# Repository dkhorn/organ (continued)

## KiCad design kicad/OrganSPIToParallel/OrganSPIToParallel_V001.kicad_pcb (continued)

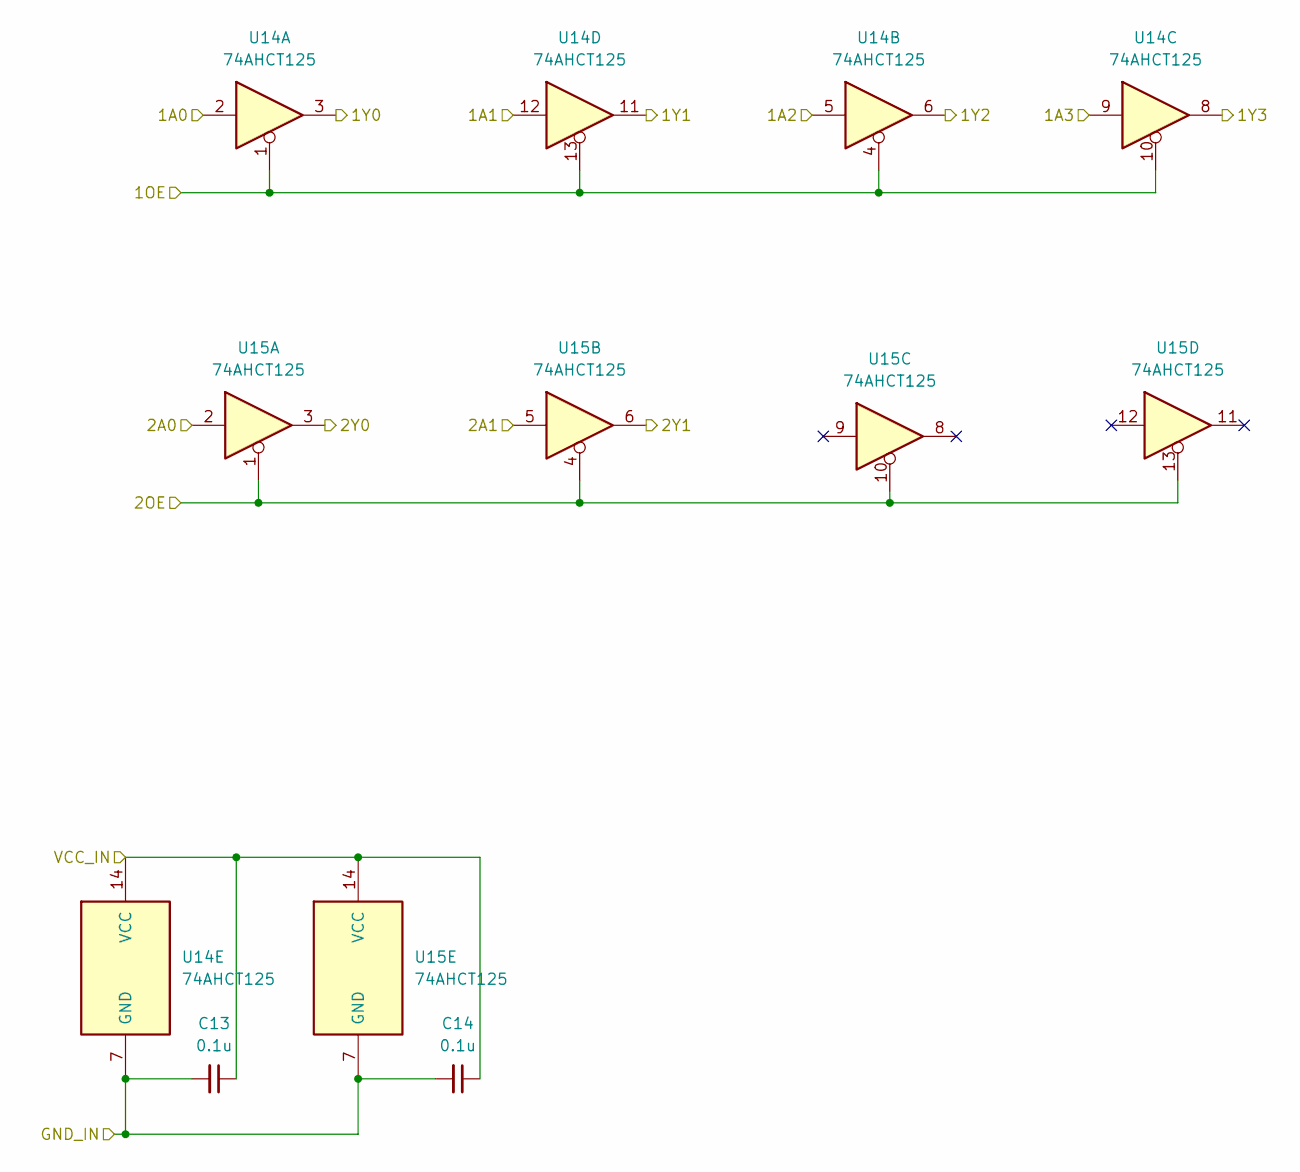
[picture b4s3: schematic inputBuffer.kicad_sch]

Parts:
C13, C14: 0.1u; C_0805_2012Metric
U14, U15: 74AHCT125; DIP-14_W7.62mm

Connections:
+5V: C13.1, C14.1, U14.14 (VCC), U15.14 (VCC); also elsewhere on the board
/CARRY_IN: U15.5; also elsewhere on the board
/LATCH_IN: U14.9; also elsewhere on the board
/MOSI_IN: U15.2; also elsewhere on the board
/OE_N_IN: U14.5; also elsewhere on the board
/SCK_IN: U14.12; also elsewhere on the board
/SRCLR_IN: U14.2; also elsewhere on the board
GND: C13.2, C14.2, U14.1, U14.4, U14.7 (GND), U14.10, U14.13, U15.1, U15.4, U15.7 (GND), U15.10, U15.13; also elsewhere on the board
G_CARRY_IN: U15.6; also elsewhere on the board
G_LATCH: U14.8; also elsewhere on the board
G_MOSI: U15.3; also elsewhere on the board
G_OE_N: U14.6; also elsewhere on the board
G_SCK: U14.11; also elsewhere on the board
G_SRCLR: U14.3; also elsewhere on the board

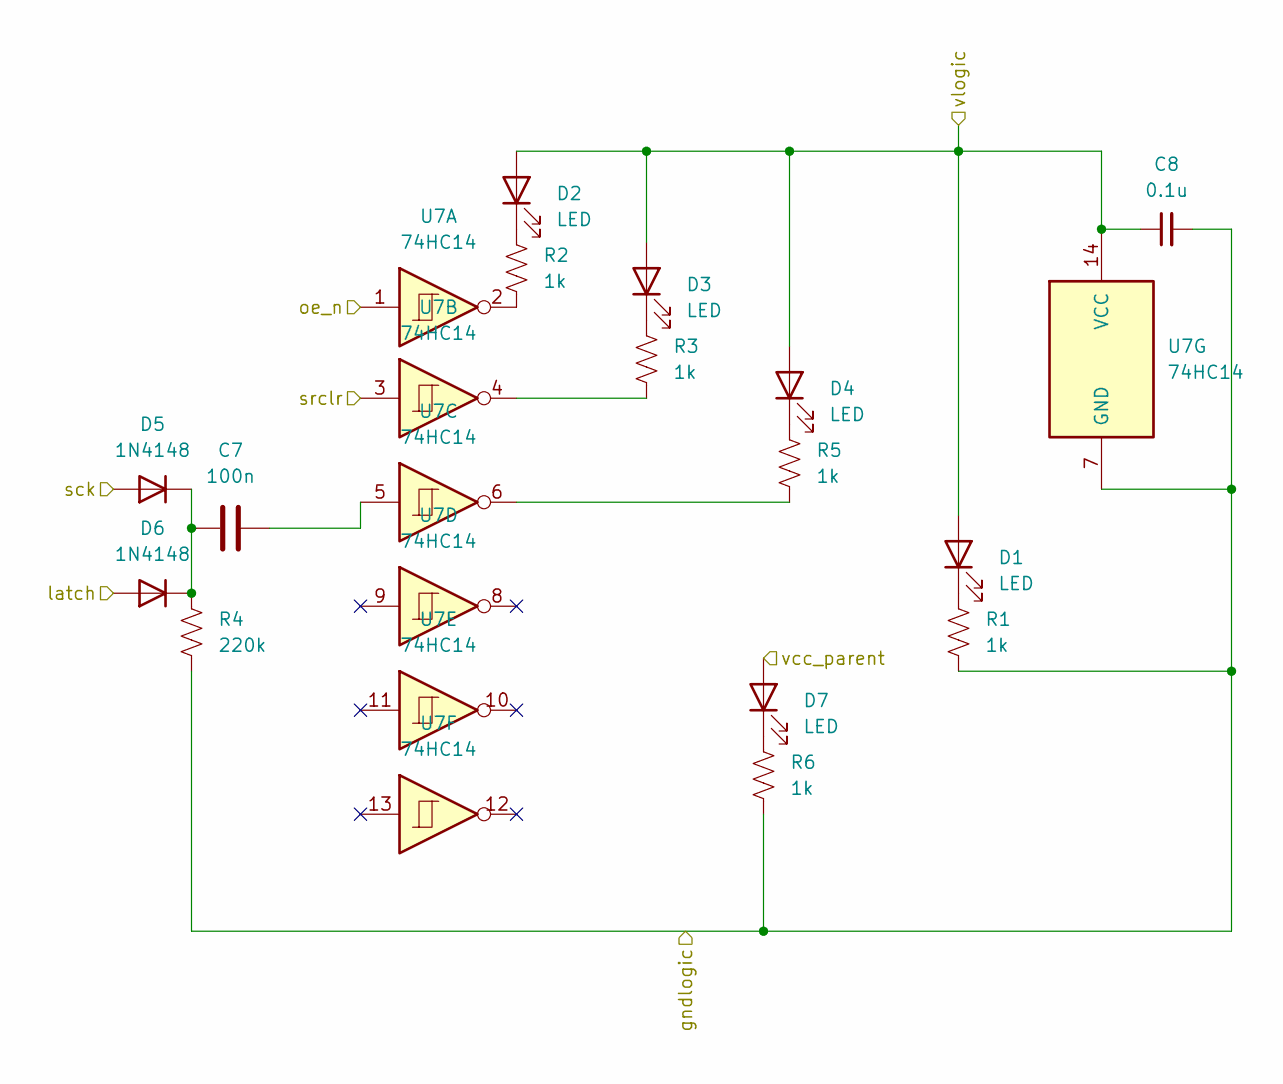
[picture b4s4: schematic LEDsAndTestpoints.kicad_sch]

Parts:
C7: 100n; C_0805_2012Metric
C8: 0.1u; C_0805_2012Metric
D1, D2, D3, D4, D7: LED; LED_0805_2012Metric
D5, D6: 1N4148; D_0805_2012Metric
R1, R2, R3, R5, R6: 1k; R_0805_2012Metric
R4: 220k; R_0805_2012Metric
U7: 74HC14; SOIC-14_3.9x8.7mm_P1.27mm

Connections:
+5V: C8.1, D1.2 (A), D2.2 (A), D3.2 (A), D4.2 (A), U7.14 (VCC); also elsewhere on the board
GND: C8.2, R1.2, R4.2, R6.2, U7.7 (GND); also elsewhere on the board
G_LATCH: D6.2 (A); also elsewhere on the board
G_OE_N: U7.1; also elsewhere on the board
G_SCK: D5.2 (A); also elsewhere on the board
G_SRCLR: U7.3; also elsewhere on the board
unnamed: C7.2, U7.5
unnamed: D1.1 (K), R1.1
unnamed: D2.1 (K), R2.1
unnamed: D3.1 (K), R3.1
unnamed: D4.1 (K), R5.1
unnamed: C7.1, D5.1 (K), D6.1 (K), R4.1
unnamed: D7.1 (K), R6.1
unnamed: R2.2, U7.2
unnamed: R3.2, U7.4
unnamed: R5.2, U7.6
VCC_PARENT: D7.2 (A); also elsewhere on the board

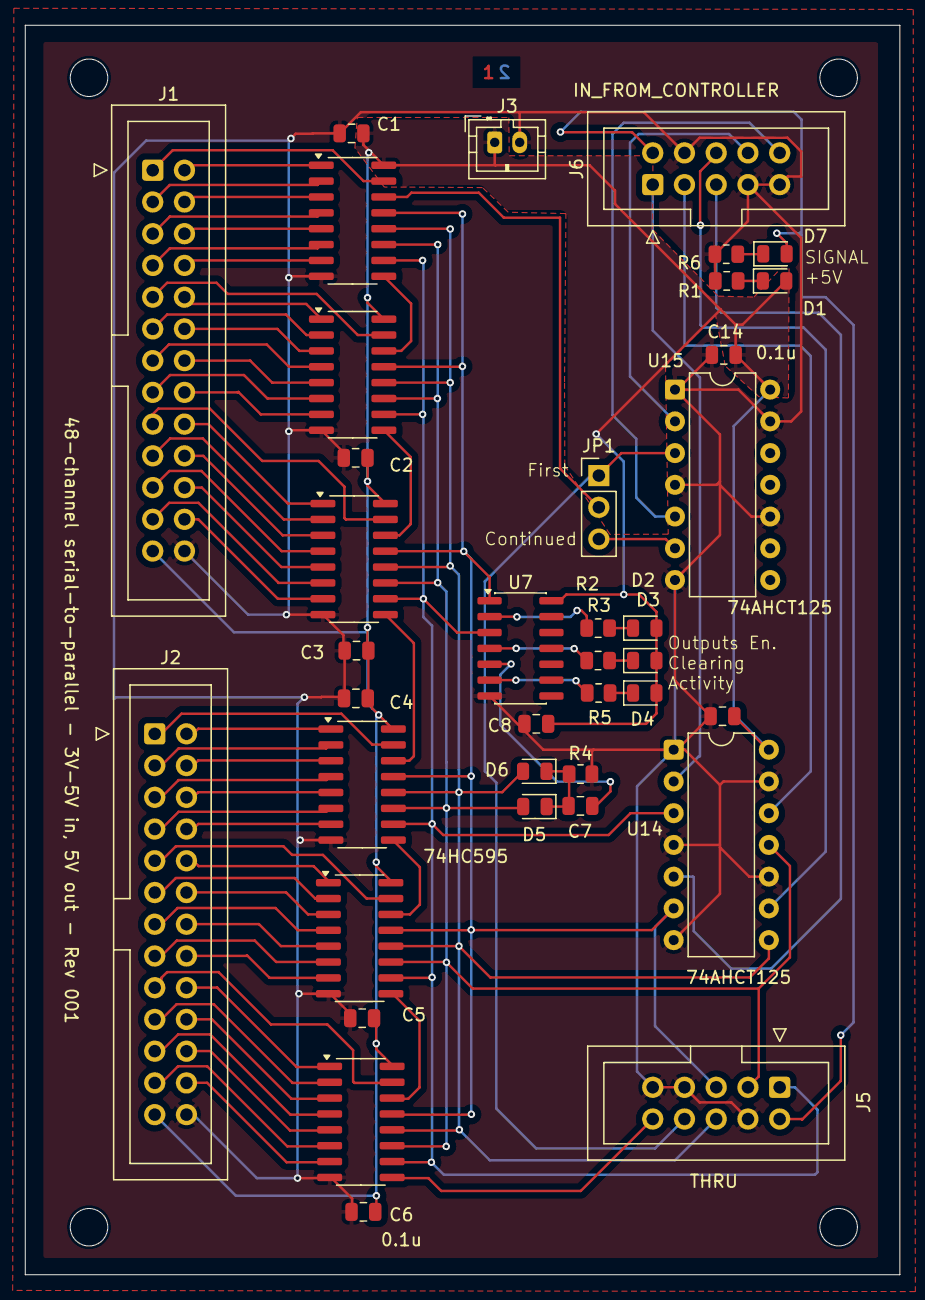
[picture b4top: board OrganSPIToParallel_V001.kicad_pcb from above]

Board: 2 copper layers, 70.0 x 100.0 mm, 38 parts (0 on the bottom side), 80 nets.

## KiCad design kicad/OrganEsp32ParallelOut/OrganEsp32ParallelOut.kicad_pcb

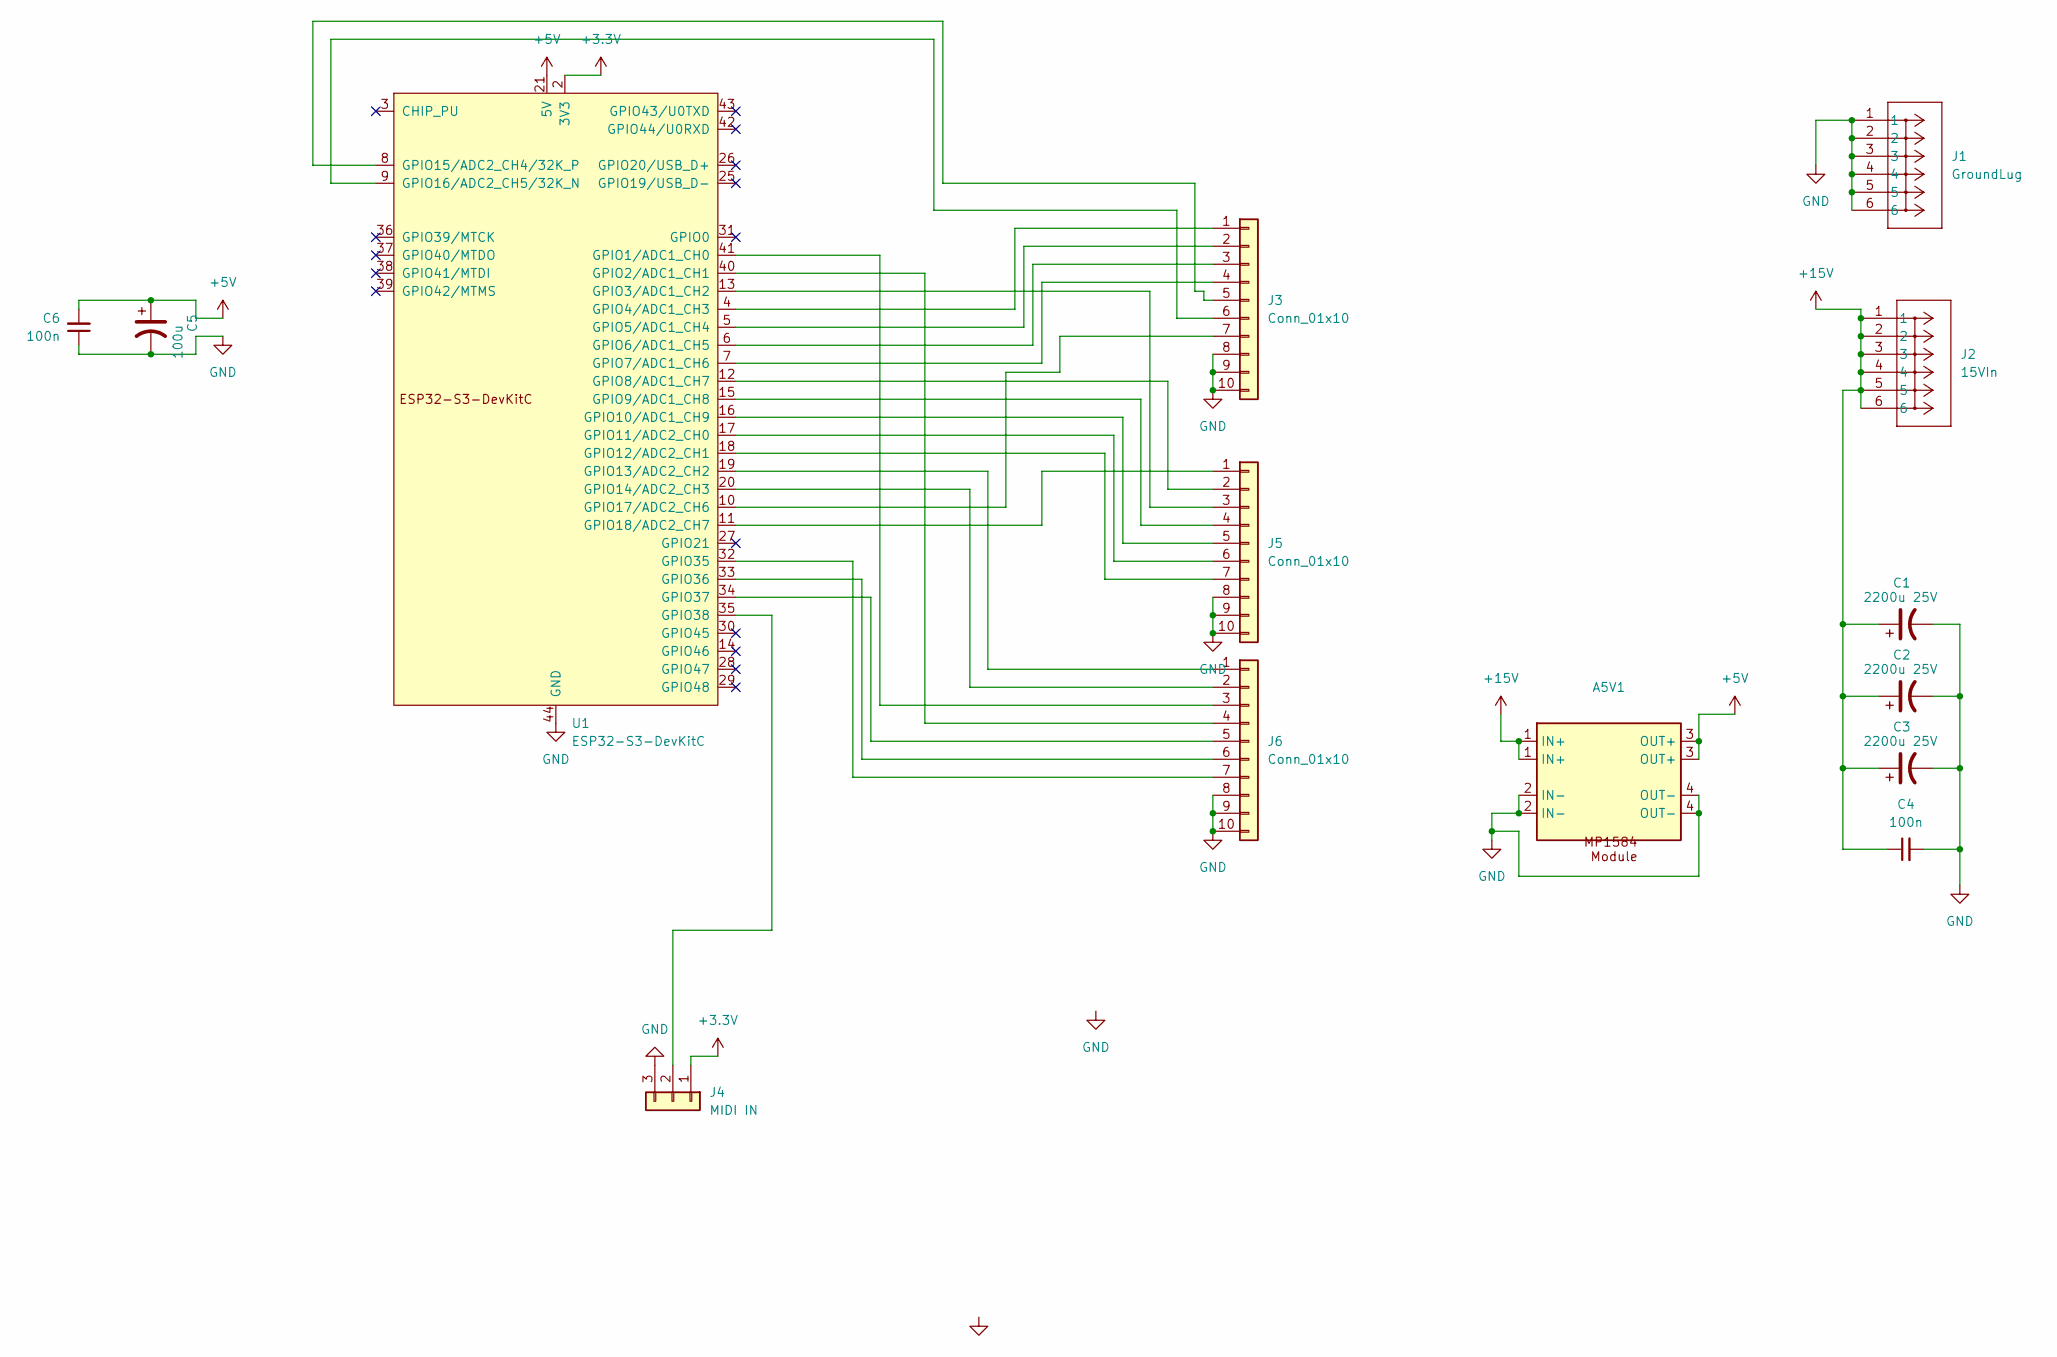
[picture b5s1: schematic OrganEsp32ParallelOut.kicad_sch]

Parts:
A5V1: MP1584_Module
C1, C2, C3: 2200u 25V; CP_Radial_D10.0mm_P5.00mm
C4, C6: 100n; C_Disc_D4.3mm_W1.9mm_P5.00mm
C5: 100u; CP_Radial_D5.0mm_P2.00mm
J1: GroundLug; CONN_8199_KEY
J2: 15VIn; CONN_8199_KEY
J3, J5, J6: Conn_01x10; IDC-Header_2x05_P2.54mm_Vertical
J4: MIDI IN; JST_PH_B3B-PH-K_1x03_P2.00mm_Vertical
U1: ESP32-S3-DevKitC

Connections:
+3.3V: J4.1, U1.1 (3V3), U1.2 (3V3)
+5V: A5V1.3 (OUT+), C5.1, C6.2, U1.21 (5V)
+15V: A5V1.1 (IN+), C1.1, C2.1, C3.1, C4.1, J2.1, J2.2, J2.3, J2.4, J2.5, J2.6
GND: A5V1.2 (IN-), A5V1.4 (OUT-), C1.2, C2.2, C3.2, C4.2, C5.2, C6.1, J1.1, J1.2, J1.3, J1.4, J1.5, J1.6, J3.8, J3.9, J3.10, J4.3, J5.8, J5.9, J5.10, J6.8, J6.9, J6.10, U1.22 (GND), U1.23 (GND), U1.24 (GND), U1.44 (GND)
unnamed: J3.1, U1.4 (GPIO4/ADC1_CH3)
unnamed: J3.2, U1.5 (GPIO5/ADC1_CH4)
unnamed: J3.3, U1.6 (GPIO6/ADC1_CH5)
unnamed: J3.4, U1.7 (GPIO7/ADC1_CH6)
unnamed: J3.5, U1.8 (GPIO15/ADC2_CH4/32K_P)
unnamed: J3.6, U1.9 (GPIO16/ADC2_CH5/32K_N)
unnamed: J3.7, U1.10 (GPIO17/ADC2_CH6)
unnamed: J4.2, U1.35 (GPIO38)
unnamed: J5.1, U1.11 (GPIO18/ADC2_CH7)
unnamed: J5.2, U1.12 (GPIO8/ADC1_CH7)
unnamed: J5.3, U1.13 (GPIO3/ADC1_CH2)
unnamed: J5.4, U1.15 (GPIO9/ADC1_CH8)
unnamed: J5.5, U1.16 (GPIO10/ADC1_CH9)
unnamed: J5.6, U1.17 (GPIO11/ADC2_CH0)
unnamed: J5.7, U1.18 (GPIO12/ADC2_CH1)
unnamed: J6.1, U1.19 (GPIO13/ADC2_CH2)
unnamed: J6.2, U1.20 (GPIO14/ADC2_CH3)
unnamed: J6.3, U1.41 (GPIO1/ADC1_CH0)
unnamed: J6.4, U1.40 (GPIO2/ADC1_CH1)
unnamed: J6.5, U1.34 (GPIO37)
unnamed: J6.6, U1.33 (GPIO36)
unnamed: J6.7, U1.32 (GPIO35)

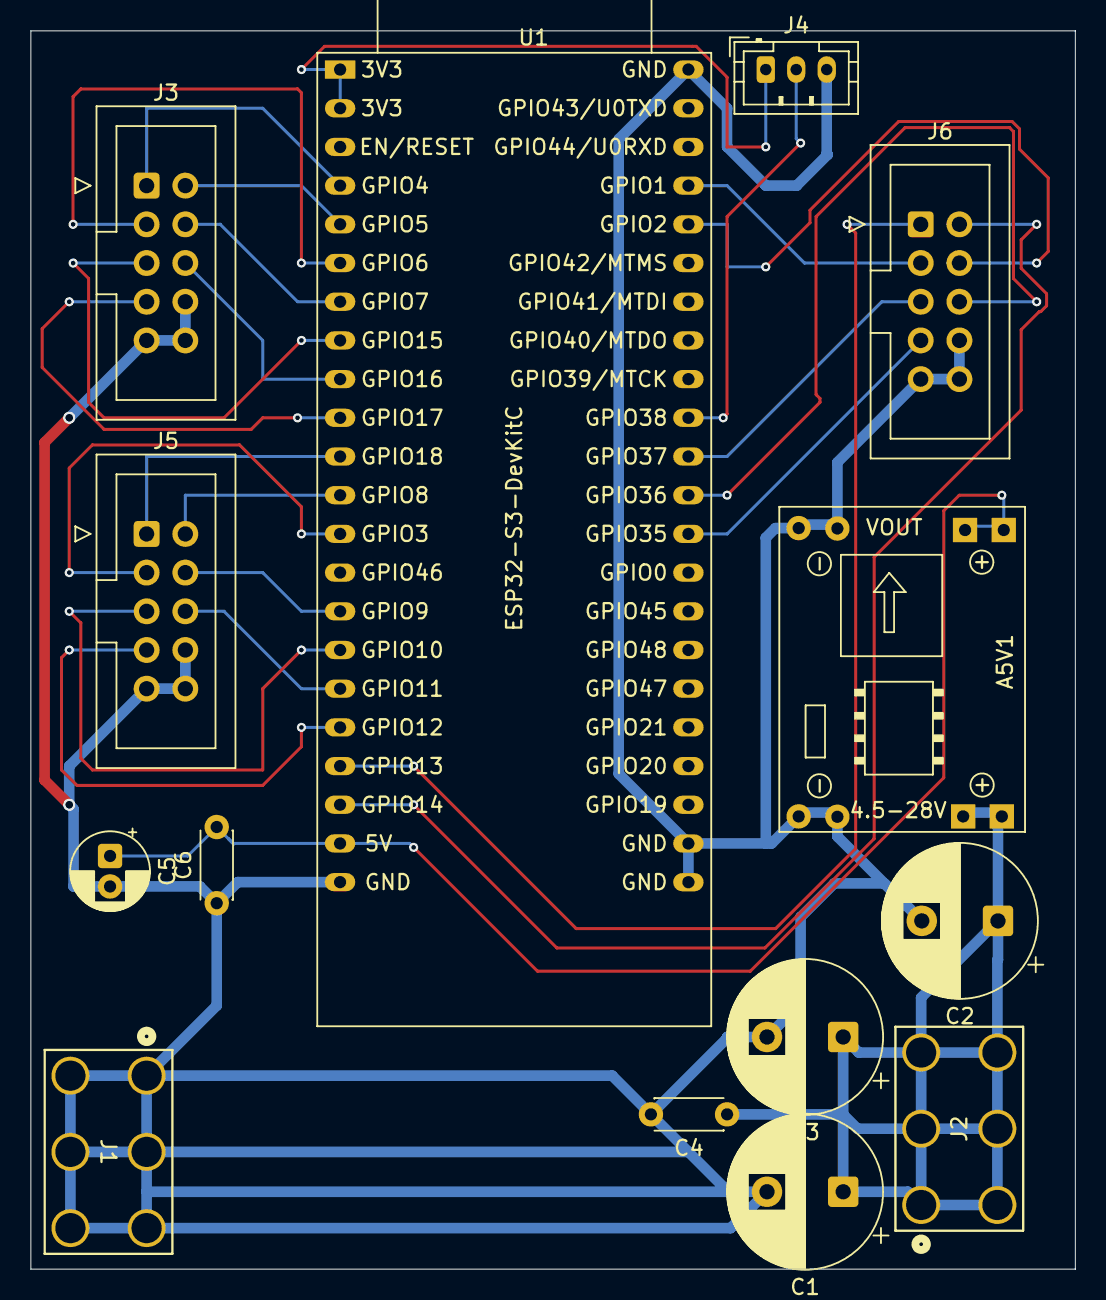
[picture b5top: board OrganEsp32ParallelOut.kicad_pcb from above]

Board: 2 copper layers, 68.6 x 81.3 mm, 14 parts (0 on the bottom side), 26 nets.

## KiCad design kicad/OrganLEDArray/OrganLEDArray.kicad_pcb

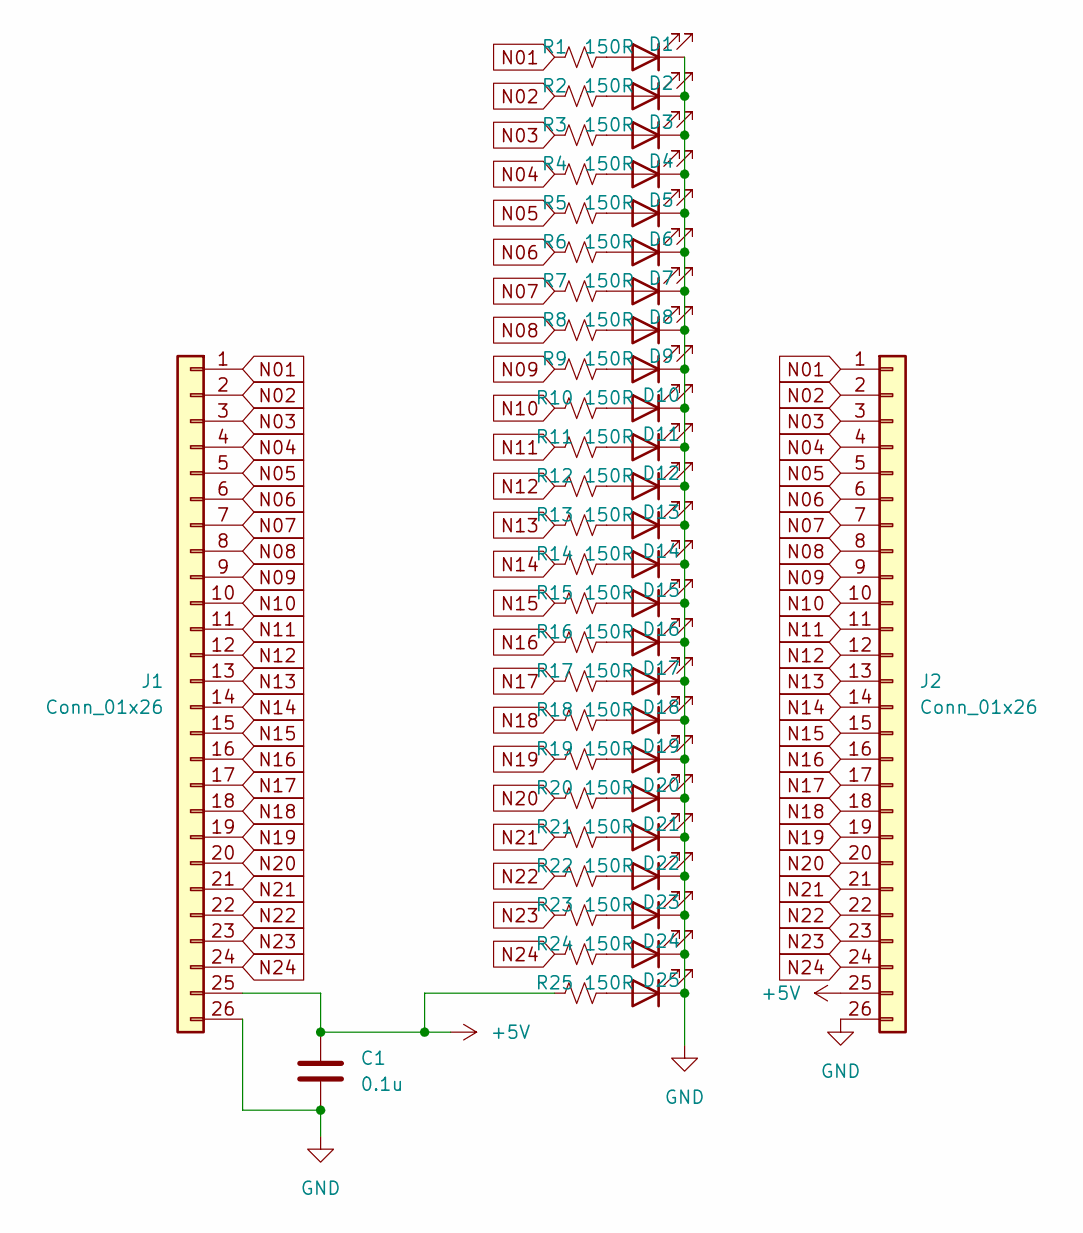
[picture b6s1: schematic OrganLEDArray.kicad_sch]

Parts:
C1: 0.1u; C_0603_1608Metric
D1, D2, D3, D4, D5, D6, D7, D8, D9, D10, D11, D12, D13, D14, D15, D16, D17, D18, D19, D20, D21, D22, D23, D24, D25: LED; LED_0603_1608Metric
J1, J2: Conn_01x26; IDC-Header_2x13_P2.54mm_Vertical
R1, R2, R3, R4, R5, R6, R7, R8, R9, R10, R11, R12, R13, R14, R15, R16, R17, R18, R19, R20, R21, R22, R23, R24, R25: 150R; R_0603_1608Metric

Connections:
+5V: C1.1, J1.25, J2.25, R25.1
GND: C1.2, D1.1 (K), D2.1 (K), D3.1 (K), D4.1 (K), D5.1 (K), D6.1 (K), D7.1 (K), D8.1 (K), D9.1 (K), D10.1 (K), D11.1 (K), D12.1 (K), D13.1 (K), D14.1 (K), D15.1 (K), D16.1 (K), D17.1 (K), D18.1 (K), D19.1 (K), D20.1 (K), D21.1 (K), D22.1 (K), D23.1 (K), D24.1 (K), D25.1 (K), J1.26, J2.26
N01: J1.1, J2.1, R1.1; also elsewhere on the board
N02: J1.2, J2.2, R2.1
N03: J1.3, J2.3, R3.1
N04: J1.4, J2.4, R4.1
N05: J1.5, J2.5, R5.1
N06: J1.6, J2.6, R6.1
N07: J1.7, J2.7, R7.1
N08: J1.8, J2.8, R8.1
N09: J1.9, J2.9, R9.1
N10: J1.10, J2.10, R10.1
N11: J1.11, J2.11, R11.1
N12: J1.12, J2.12, R12.1
N13: J1.13, J2.13, R13.1
N14: J1.14, J2.14, R14.1
N15: J1.15, J2.15, R15.1
N16: J1.16, J2.16, R16.1
N17: J1.17, J2.17, R17.1
N18: J1.18, J2.18, R18.1
N19: J1.19, J2.19, R19.1
N20: J1.20, J2.20, R20.1
N21: J1.21, J2.21, R21.1
N22: J1.22, J2.22, R22.1
N23: J1.23, J2.23, R23.1
N24: J1.24, J2.24, R24.1
unnamed 26: D1.2 (A), R1.2; also elsewhere on the board
unnamed: D2.2 (A), R2.2
unnamed: D3.2 (A), R3.2
unnamed: D4.2 (A), R4.2
unnamed: D5.2 (A), R5.2
unnamed: D6.2 (A), R6.2
unnamed: D7.2 (A), R7.2
unnamed: D8.2 (A), R8.2
unnamed: D9.2 (A), R9.2
unnamed: D10.2 (A), R10.2
unnamed: D11.2 (A), R11.2
unnamed: D12.2 (A), R12.2
unnamed: D13.2 (A), R13.2
unnamed: D14.2 (A), R14.2
unnamed: D15.2 (A), R15.2
unnamed: D16.2 (A), R16.2
unnamed: D17.2 (A), R17.2
unnamed: D18.2 (A), R18.2
unnamed: D19.2 (A), R19.2
unnamed: D20.2 (A), R20.2
unnamed: D21.2 (A), R21.2
unnamed: D22.2 (A), R22.2
unnamed: D23.2 (A), R23.2
unnamed: D24.2 (A), R24.2
unnamed: D25.2 (A), R25.2

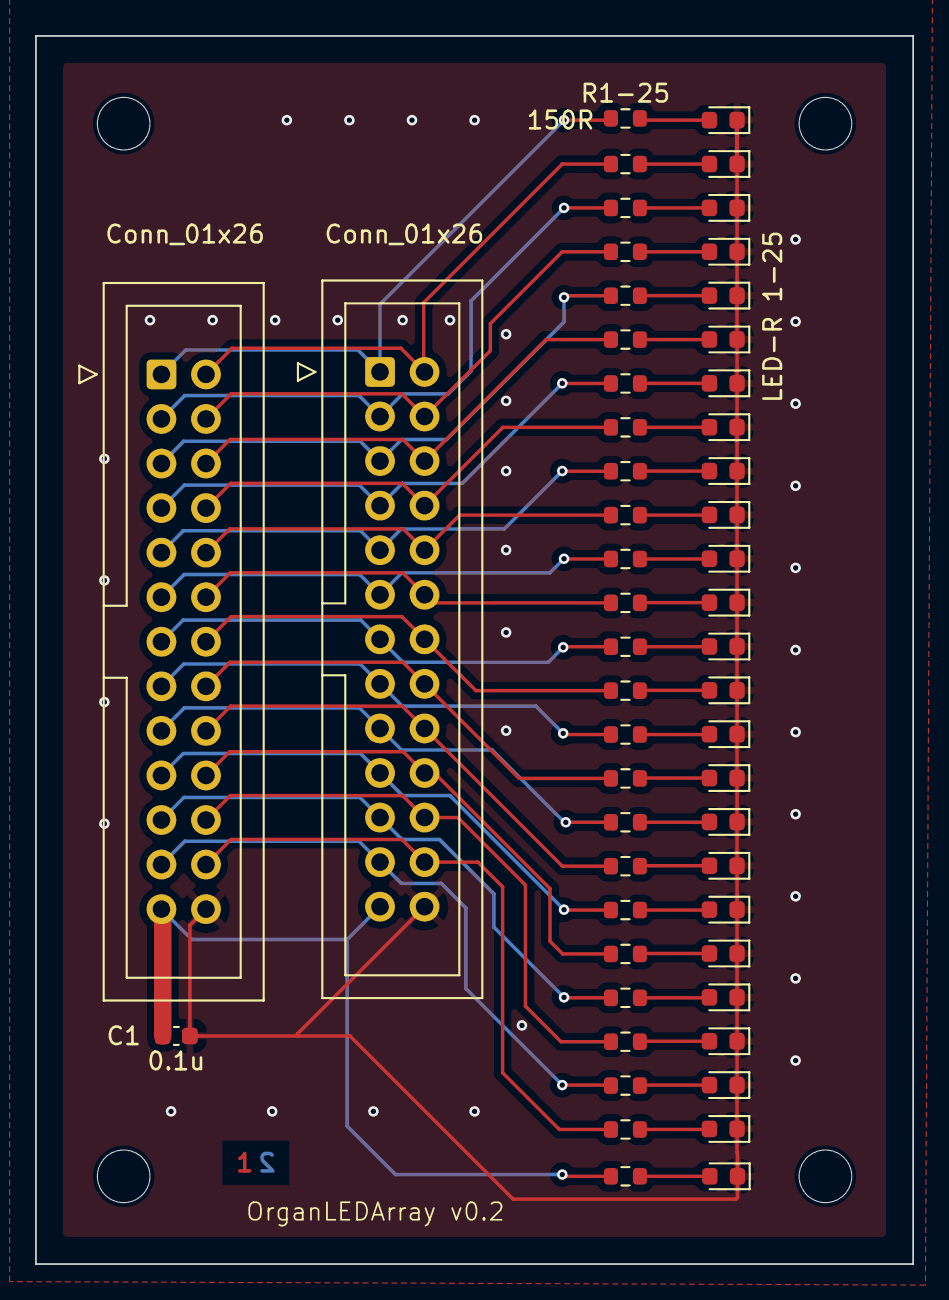
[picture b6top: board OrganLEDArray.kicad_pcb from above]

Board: 2 copper layers, 50.0 x 70.0 mm, 53 parts (0 on the bottom side), 51 nets.

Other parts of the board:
R1-25: 150R; R_0603_1608Metric

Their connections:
N01: R1-25.1; also elsewhere on the board
unnamed 26: R1-25.2; also elsewhere on the board

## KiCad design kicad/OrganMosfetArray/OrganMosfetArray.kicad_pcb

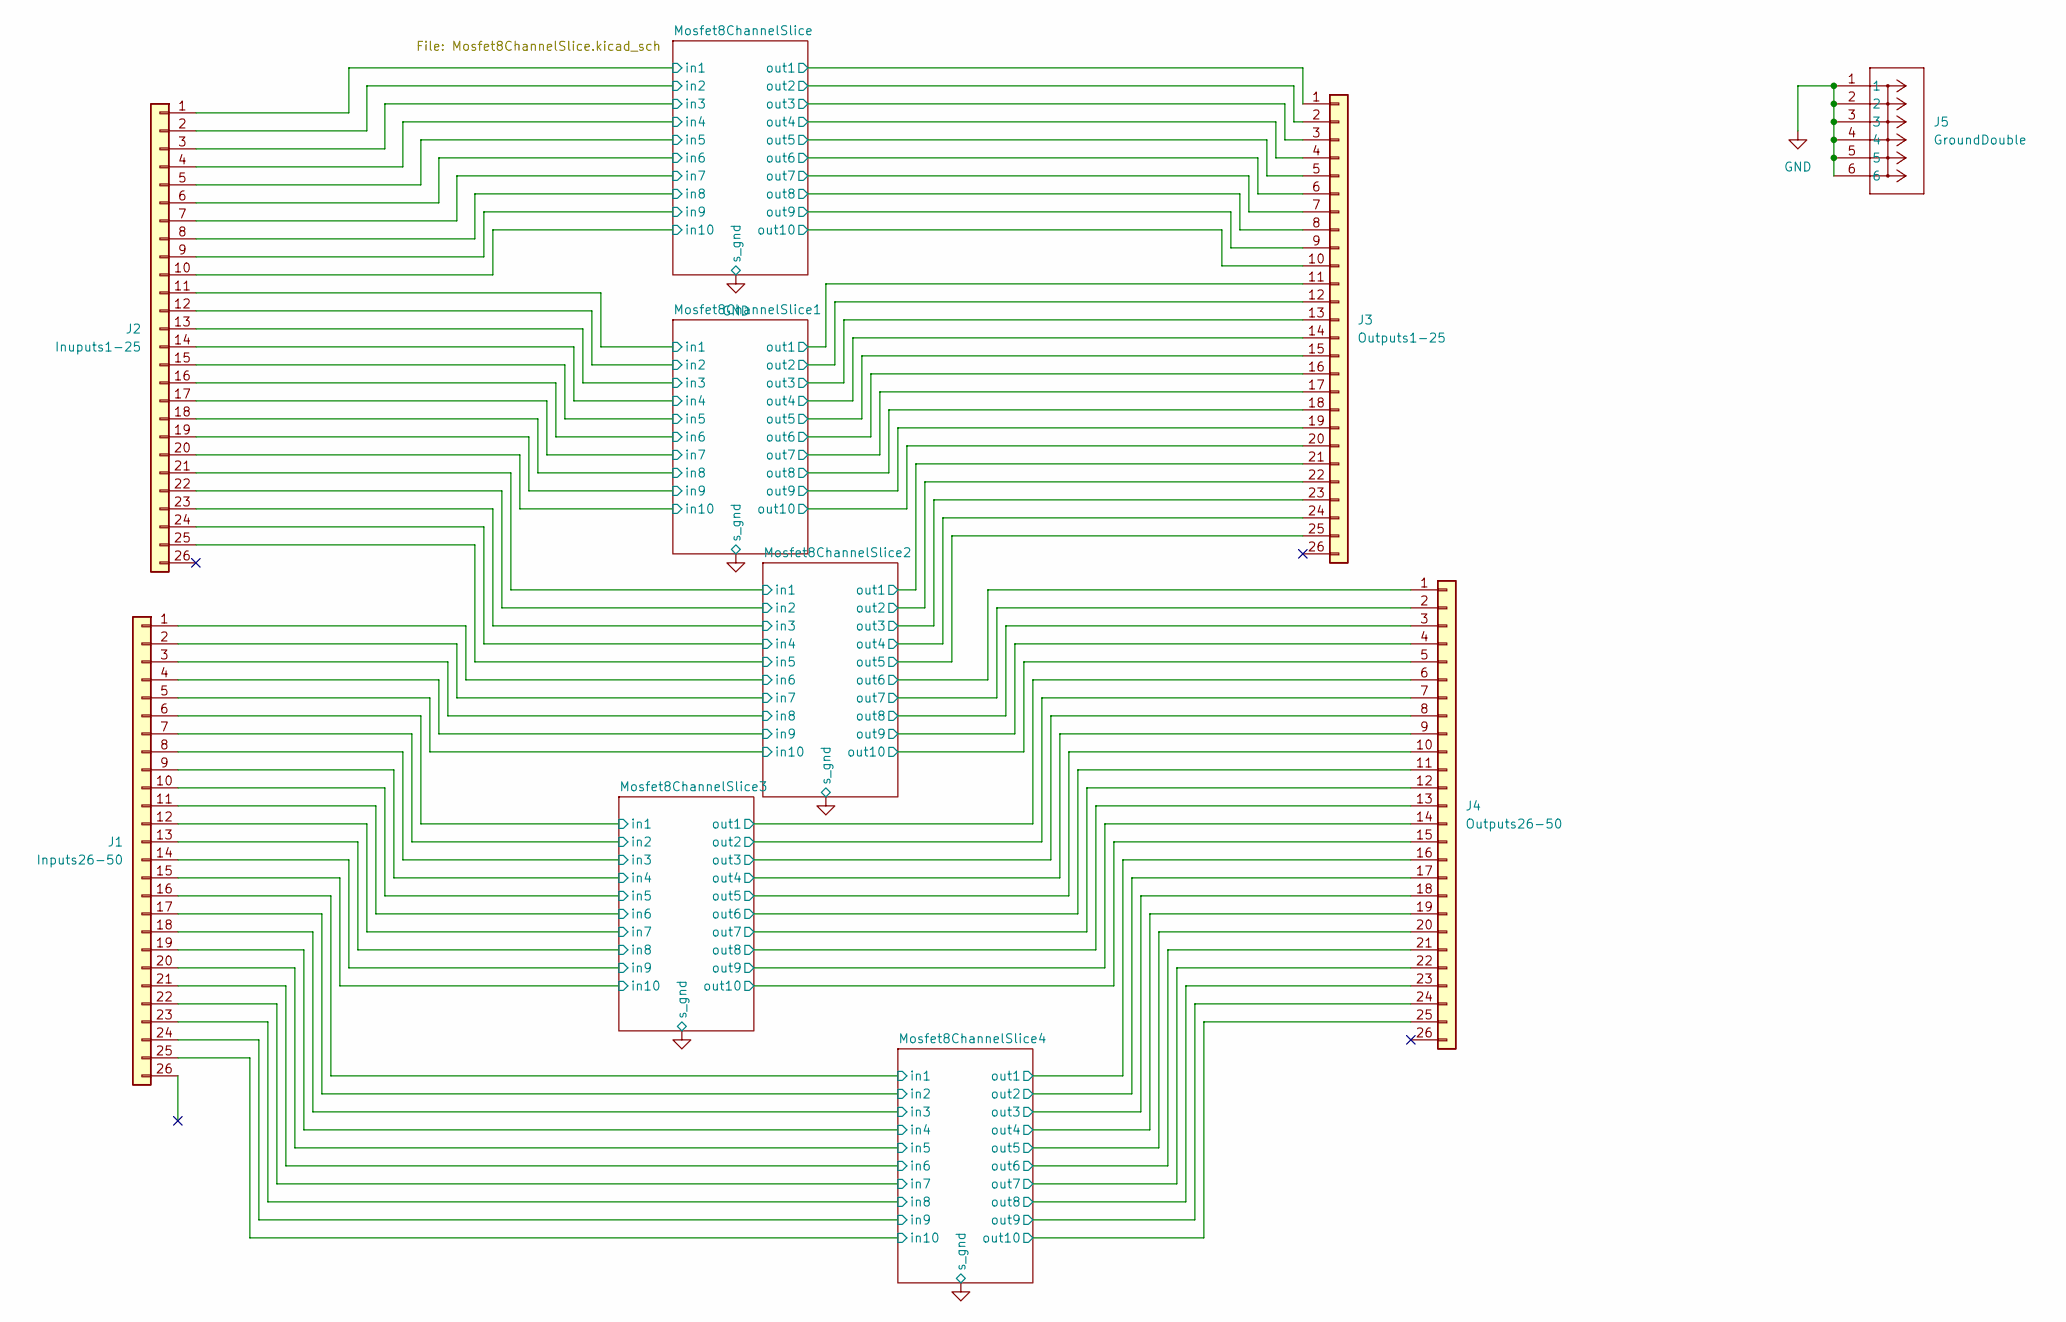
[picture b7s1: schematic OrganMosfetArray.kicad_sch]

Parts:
J1: Inputs26-50; IDC-Header_2x13_P2.54mm_Vertical
J2: Inuputs1-25; IDC-Header_2x13_P2.54mm_Vertical
J3: Outputs1-25; IDC-Header_2x13_P2.54mm_Vertical
J4: Outputs26-50; IDC-Header_2x13_P2.54mm_Vertical
J5: GroundDouble; CONN_8199_KEY

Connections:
/Mosfet8ChannelSlice1/in1: J2.11; also elsewhere on the board
/Mosfet8ChannelSlice1/in2: J2.12; also elsewhere on the board
/Mosfet8ChannelSlice1/in3: J2.13; also elsewhere on the board
/Mosfet8ChannelSlice1/in4: J2.14; also elsewhere on the board
/Mosfet8ChannelSlice1/in5: J2.15; also elsewhere on the board
/Mosfet8ChannelSlice1/in6: J2.16; also elsewhere on the board
/Mosfet8ChannelSlice1/in7: J2.17; also elsewhere on the board
/Mosfet8ChannelSlice1/in8: J2.18; also elsewhere on the board
/Mosfet8ChannelSlice1/in9: J2.19; also elsewhere on the board
/Mosfet8ChannelSlice1/in10: J2.20; also elsewhere on the board
/Mosfet8ChannelSlice1/out1: J3.11; also elsewhere on the board
/Mosfet8ChannelSlice1/out2: J3.12; also elsewhere on the board
/Mosfet8ChannelSlice1/out3: J3.13; also elsewhere on the board
/Mosfet8ChannelSlice1/out4: J3.14; also elsewhere on the board
/Mosfet8ChannelSlice1/out5: J3.15; also elsewhere on the board
/Mosfet8ChannelSlice1/out6: J3.16; also elsewhere on the board
/Mosfet8ChannelSlice1/out7: J3.17; also elsewhere on the board
/Mosfet8ChannelSlice1/out8: J3.18; also elsewhere on the board
/Mosfet8ChannelSlice1/out9: J3.19; also elsewhere on the board
/Mosfet8ChannelSlice1/out10: J3.20; also elsewhere on the board
/Mosfet8ChannelSlice2/in1: J2.21; also elsewhere on the board
/Mosfet8ChannelSlice2/in2: J2.22; also elsewhere on the board
/Mosfet8ChannelSlice2/in3: J2.23; also elsewhere on the board
/Mosfet8ChannelSlice2/in4: J2.24; also elsewhere on the board
/Mosfet8ChannelSlice2/in5: J2.25; also elsewhere on the board
/Mosfet8ChannelSlice2/in6: J1.1; also elsewhere on the board
/Mosfet8ChannelSlice2/in7: J1.2; also elsewhere on the board
/Mosfet8ChannelSlice2/in8: J1.3; also elsewhere on the board
/Mosfet8ChannelSlice2/in9: J1.4; also elsewhere on the board
/Mosfet8ChannelSlice2/in10: J1.5; also elsewhere on the board
/Mosfet8ChannelSlice2/out1: J3.21; also elsewhere on the board
/Mosfet8ChannelSlice2/out2: J3.22; also elsewhere on the board
/Mosfet8ChannelSlice2/out3: J3.23; also elsewhere on the board
/Mosfet8ChannelSlice2/out4: J3.24; also elsewhere on the board
/Mosfet8ChannelSlice2/out5: J3.25; also elsewhere on the board
/Mosfet8ChannelSlice2/out6: J4.1; also elsewhere on the board
/Mosfet8ChannelSlice2/out7: J4.2; also elsewhere on the board
/Mosfet8ChannelSlice2/out8: J4.3; also elsewhere on the board
/Mosfet8ChannelSlice2/out9: J4.4; also elsewhere on the board
/Mosfet8ChannelSlice2/out10: J4.5; also elsewhere on the board
/Mosfet8ChannelSlice3/in1: J1.6; also elsewhere on the board
/Mosfet8ChannelSlice3/in2: J1.7; also elsewhere on the board
/Mosfet8ChannelSlice3/in3: J1.8; also elsewhere on the board
/Mosfet8ChannelSlice3/in4: J1.9; also elsewhere on the board
/Mosfet8ChannelSlice3/in5: J1.10; also elsewhere on the board
/Mosfet8ChannelSlice3/in6: J1.11; also elsewhere on the board
/Mosfet8ChannelSlice3/in7: J1.12; also elsewhere on the board
/Mosfet8ChannelSlice3/in8: J1.13; also elsewhere on the board
/Mosfet8ChannelSlice3/in9: J1.14; also elsewhere on the board
/Mosfet8ChannelSlice3/in10: J1.15; also elsewhere on the board
/Mosfet8ChannelSlice3/out1: J4.6; also elsewhere on the board
/Mosfet8ChannelSlice3/out2: J4.7; also elsewhere on the board
/Mosfet8ChannelSlice3/out3: J4.8; also elsewhere on the board
/Mosfet8ChannelSlice3/out4: J4.9; also elsewhere on the board
/Mosfet8ChannelSlice3/out5: J4.10; also elsewhere on the board
/Mosfet8ChannelSlice3/out6: J4.11; also elsewhere on the board
/Mosfet8ChannelSlice3/out7: J4.12; also elsewhere on the board
/Mosfet8ChannelSlice3/out8: J4.13; also elsewhere on the board
/Mosfet8ChannelSlice3/out9: J4.14; also elsewhere on the board
/Mosfet8ChannelSlice3/out10: J4.15; also elsewhere on the board
/Mosfet8ChannelSlice4/in1: J1.16; also elsewhere on the board
/Mosfet8ChannelSlice4/in2: J1.17; also elsewhere on the board
/Mosfet8ChannelSlice4/in3: J1.18; also elsewhere on the board
/Mosfet8ChannelSlice4/in4: J1.19; also elsewhere on the board
/Mosfet8ChannelSlice4/in5: J1.20; also elsewhere on the board
/Mosfet8ChannelSlice4/in6: J1.21; also elsewhere on the board
/Mosfet8ChannelSlice4/in7: J1.22; also elsewhere on the board
/Mosfet8ChannelSlice4/in8: J1.23; also elsewhere on the board
/Mosfet8ChannelSlice4/in9: J1.24; also elsewhere on the board
/Mosfet8ChannelSlice4/in10: J1.25; also elsewhere on the board
/Mosfet8ChannelSlice4/out1: J4.16; also elsewhere on the board
/Mosfet8ChannelSlice4/out2: J4.17; also elsewhere on the board
/Mosfet8ChannelSlice4/out3: J4.18; also elsewhere on the board
/Mosfet8ChannelSlice4/out4: J4.19; also elsewhere on the board
/Mosfet8ChannelSlice4/out5: J4.20; also elsewhere on the board
/Mosfet8ChannelSlice4/out6: J4.21; also elsewhere on the board
/Mosfet8ChannelSlice4/out7: J4.22; also elsewhere on the board
/Mosfet8ChannelSlice4/out8: J4.23; also elsewhere on the board
/Mosfet8ChannelSlice4/out9: J4.24; also elsewhere on the board
/Mosfet8ChannelSlice4/out10: J4.25; also elsewhere on the board
/Mosfet8ChannelSlice/in1: J2.1; also elsewhere on the board
/Mosfet8ChannelSlice/in2: J2.2; also elsewhere on the board
/Mosfet8ChannelSlice/in3: J2.3; also elsewhere on the board
/Mosfet8ChannelSlice/in4: J2.4; also elsewhere on the board
/Mosfet8ChannelSlice/in5: J2.5; also elsewhere on the board
/Mosfet8ChannelSlice/in6: J2.6; also elsewhere on the board
/Mosfet8ChannelSlice/in7: J2.7; also elsewhere on the board
/Mosfet8ChannelSlice/in8: J2.8; also elsewhere on the board
/Mosfet8ChannelSlice/in9: J2.9; also elsewhere on the board
/Mosfet8ChannelSlice/in10: J2.10; also elsewhere on the board
/Mosfet8ChannelSlice/out1: J3.1; also elsewhere on the board
/Mosfet8ChannelSlice/out2: J3.2; also elsewhere on the board
/Mosfet8ChannelSlice/out3: J3.3; also elsewhere on the board
/Mosfet8ChannelSlice/out4: J3.4; also elsewhere on the board
/Mosfet8ChannelSlice/out5: J3.5; also elsewhere on the board
/Mosfet8ChannelSlice/out6: J3.6; also elsewhere on the board
/Mosfet8ChannelSlice/out7: J3.7; also elsewhere on the board
/Mosfet8ChannelSlice/out8: J3.8; also elsewhere on the board
/Mosfet8ChannelSlice/out9: J3.9; also elsewhere on the board
/Mosfet8ChannelSlice/out10: J3.10; also elsewhere on the board
GND: J5.1, J5.2, J5.3, J5.4, J5.5, J5.6; also elsewhere on the board
